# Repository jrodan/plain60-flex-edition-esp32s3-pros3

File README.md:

# Plain60 Flex Edition rev2.2

## Customizing

Changed the PCB to be able to use the proS3 controller https://esp32s3.com/pros3.html and provide I2C ports and the side of the pcb together with 3 PINs directly accessible via PCB for RGB underglow lights. 

| LCSC part # | Description   | Value | Package  | Amount |
| ----------- | ------------- | ----- | -------- | ------:|
| C109001     | Diode         |       | 0805     | 65     |

## General

This universal 60% PCB is designed to support as little layouts as possible without limiting usability for most users. The reason I did this is because other PCBs made for this form factor usually have so many supported layouts that it could almost qualify as swiss cheese.

It also features a fuse and an ESD protection chip to protect the MCU and other parts of the PCB.

## Features
- Fits in the TGR Unikorn
- Compatible with QMK Firmware and VIA Configurator (if you flash a VIA compatible .hex file)
- Compatible with most universal 60% cases and HHKB/WKL Tofu by KBDfans
- USB type-C
- Optional JST header for connection with daughterboard
- Footprint for optional speaker (AST1109MLTRQ)
- ESD protection and fuse
- No LEDs and no underglow
- Minimal layout support
- ISP header

## Supported layouts

## Building
If you feel like building a few of these PCBs yourself, go to the 'Releases' tab and download the latest gerber files. Order those at your favourite PCB manufacturer, get the components needed (see below) and solder them on! A hot air station is not required but a soldering iron is. Flux is recommended.

## Opening the project
To open the files you will need the latest KiCAD nightly version.

## Bill of materials (BOM)
Amount is per PCB, multiply as needed.

| LCSC part # | Description   | Value | Package  | Amount |
| ----------- | ------------- | ----- | -------- | ------:|
| C128353     | Capacitor     | 0.1uF | 0805     | 4      |
| C131056     | Capacitor     | 4.7uF | 0805     | 1      |
| C215803     | Capacitor     | 1uF   | 0805     | 1      |
| C109001     | Diode         |       | 0805     | 65     |
| C261942     | Fuse          |       | 0805     | 1      |
| C165948     | Connector     |       | SMD/THT  | 1      |
| C103904     | Resistor      | 10K   | 0805     | 2      |
| C212411     | Resistor      | 5.1K  | 0805     | 2      |
| C325772     | Resistor      | 22    | 0805     | 2      |
| C44854      | MCU           | 32U4  | QFP-44   | 1      |
| C7519       | ESD chip      |       | SOT23-6  | 1      |
| C341521     | Resonator     | 16MHz | SMD      | 1      |
| C92584      | Switch        |       | SMD      | 1      |
| C160404     | Optional JST  |       | SMD      | 1      |

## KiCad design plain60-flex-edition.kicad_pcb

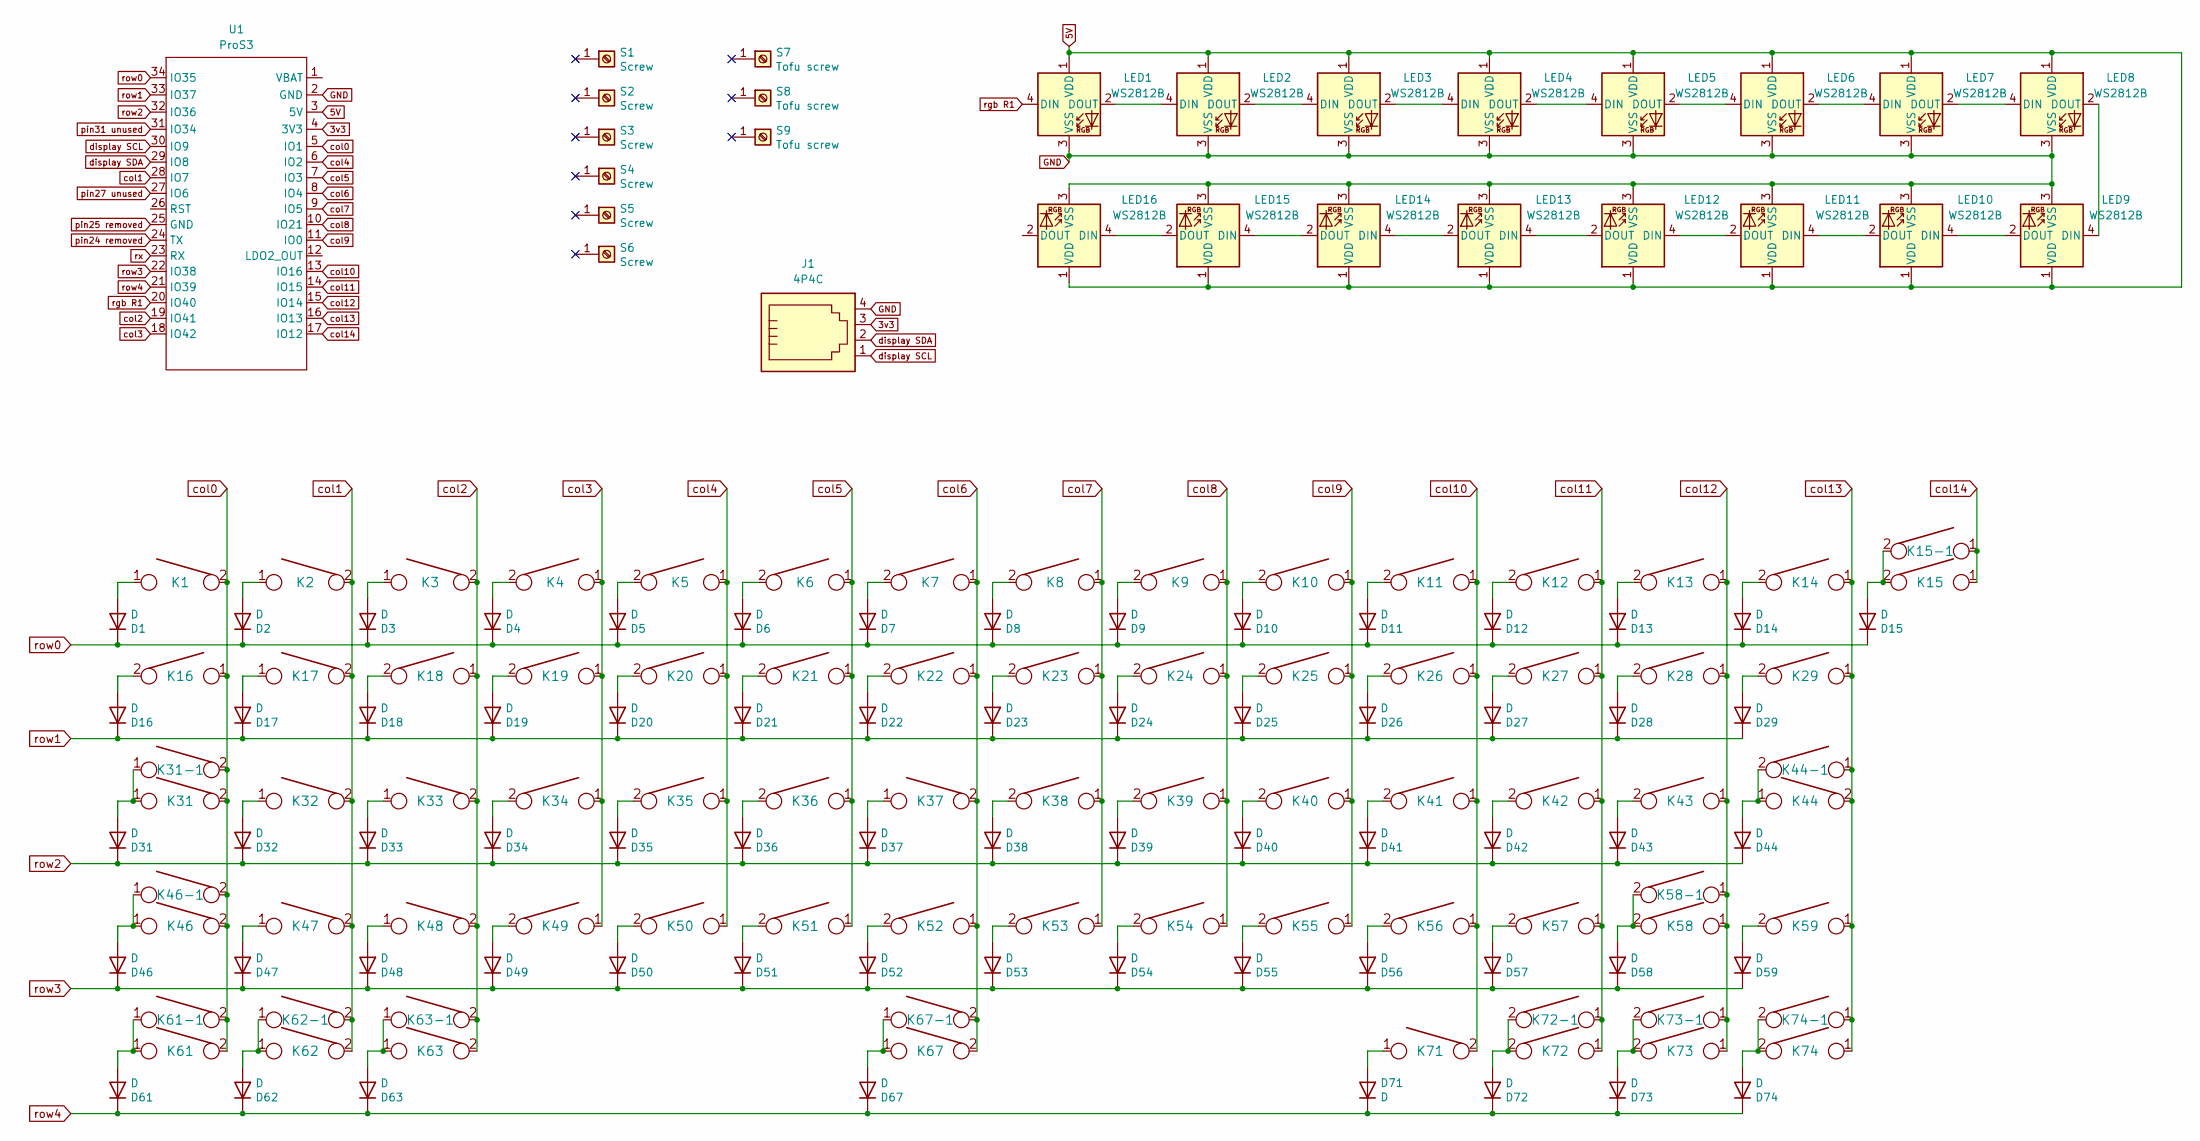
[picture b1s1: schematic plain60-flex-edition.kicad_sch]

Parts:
D1, D2, D3, D4, D5, D6, D7, D8, D9, D10, D11, D12, D13, D14, D15, D16, D17, D18, D19, D20, D21, D22, D23, D24, D25, D26, D27, D28, D29, D31, D32, D33, D34, D35, D36, D37, D38, D39, D40, D41, D42, D43, D44, D46, D47, D48, D49, D50, D51, D52, D53, D54, D55, D56, D57, D58, D59, D61, D62, D63, D67, D71, D72, D73, D74: D; D_0805
J1: 4P4C; JST_PH_S4B-PH-K_1x04_P2.00mm_Horizontal
K1, K2, K3, K4, K5, K6, K7, K8, K9, K10, K11, K12, K13, K14, K15-1, K17, K18, K19, K20, K21, K22, K23, K24, K25, K26, K27, K28, K32, K33, K34, K35, K36, K37, K38, K39, K40, K41, K42, K43, K47, K48, K49, K50, K51, K52, K53, K54, K55, K56, K57, K59, K62-1, K73-1: KEYSW; CHERRY_PLATE_100H
K15: KEYSW; CHERRY_PCB_200H
K16, K29, K61-1, K63-1, K72-1, K74-1: KEYSW; CHERRY_PLATE_150H
K31, K58-1: KEYSW; CHERRY_PLATE_175H
K31-1, K46-1, K61, K62, K63, K71, K72, K73, K74: KEYSW; CHERRY_PLATE_125H
K44: KEYSW; CHERRY_PCB_225H_F
K44-1: KEYSW; CHERRY_PCB_200H_V
K46: KEYSW; CHERRY_PCB_225H
K58: KEYSW; CHERRY_PCB_275H
K67: KEYSW; CHERRY_PCB_625H_F
K67-1: KEYSW; CHERRY_PCB_700H_F
LED1, LED2, LED3, LED4, LED5, LED6, LED7, LED8, LED9, LED10, LED11, LED12, LED13, LED14, LED15, LED16: WS2812B; LED_WS2812B_PLCC4_5.0x5.0mm_P3.2mm
S1, S2, S3, S6: Screw; 5.5_5x2.5mm
S4, S5: Screw; 10x5_7x2.5mm
S7, S8, S9: Tofu screw; 5.5_5x2.5mm
U1: ProS3; ProS3_TH

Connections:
3v3: J1.3, U1.4 (3V3)
5V: LED1.1 (VDD), LED2.1 (VDD), LED3.1 (VDD), LED4.1 (VDD), LED5.1 (VDD), LED6.1 (VDD), LED7.1 (VDD), LED8.1 (VDD), LED9.1 (VDD), LED10.1 (VDD), LED11.1 (VDD), LED12.1 (VDD), LED13.1 (VDD), LED14.1 (VDD), LED15.1 (VDD), LED16.1 (VDD), U1.3 (5V)
GND: J1.4, LED1.3 (VSS), LED2.3 (VSS), LED3.3 (VSS), LED4.3 (VSS), LED5.3 (VSS), LED6.3 (VSS), LED7.3 (VSS), LED8.3 (VSS), LED9.3 (VSS), LED10.3 (VSS), LED11.3 (VSS), LED12.3 (VSS), LED13.3 (VSS), LED14.3 (VSS), LED15.3 (VSS), LED16.3 (VSS), U1.2 (GND)
unnamed: D1.2 (A), K1.1
unnamed: D2.2 (A), K2.1
unnamed: D3.2 (A), K3.1
unnamed: D4.2 (A), K4.2
unnamed: D5.2 (A), K5.2
unnamed: D6.2 (A), K6.2
unnamed: D7.2 (A), K7.2
unnamed: D8.2 (A), K8.2
unnamed: D9.2 (A), K9.2
unnamed: D10.2 (A), K10.2
unnamed: D11.2 (A), K11.2
unnamed: D12.2 (A), K12.2
unnamed: D13.2 (A), K13.2
unnamed: D14.2 (A), K14.2
unnamed: D15.2 (A), K15.2, K15-1.2
unnamed: D16.2 (A), K16.2
unnamed: D17.2 (A), K17.1
unnamed: D18.2 (A), K18.2
unnamed: D19.2 (A), K19.2
unnamed: D20.2 (A), K20.2
unnamed: D21.2 (A), K21.2
unnamed: D22.2 (A), K22.2
unnamed: D23.2 (A), K23.2
unnamed: D24.2 (A), K24.2
unnamed: D25.2 (A), K25.2
unnamed: D26.2 (A), K26.2
unnamed: D27.2 (A), K27.2
unnamed: D28.2 (A), K28.2
unnamed: D29.2 (A), K29.2
unnamed: D31.2 (A), K31.1, K31-1.1
unnamed: D32.2 (A), K32.1
unnamed: D33.2 (A), K33.1
unnamed: D34.2 (A), K34.2
unnamed: D35.2 (A), K35.2
unnamed: D36.2 (A), K36.2
unnamed: D37.2 (A), K37.1
unnamed: D38.2 (A), K38.2
unnamed: D39.2 (A), K39.2
unnamed: D40.2 (A), K40.2
unnamed: D41.2 (A), K41.2
unnamed: D42.2 (A), K42.2
unnamed: D43.2 (A), K43.2
unnamed: D44.2 (A), K44.1, K44-1.2
unnamed: D46.2 (A), K46.1, K46-1.1
unnamed: D47.2 (A), K47.1
unnamed: D48.2 (A), K48.1
unnamed: D49.2 (A), K49.2
unnamed: D50.2 (A), K50.2
unnamed: D51.2 (A), K51.2
unnamed: D52.2 (A), K52.2
unnamed: D53.2 (A), K53.2
unnamed: D54.2 (A), K54.2
unnamed: D55.2 (A), K55.2
unnamed: D56.2 (A), K56.2
unnamed: D57.2 (A), K57.2
unnamed: D58.2 (A), K58.2, K58-1.2
unnamed: D59.2 (A), K59.2
unnamed: D61.2 (A), K61.1, K61-1.1
unnamed: D62.2 (A), K62.1, K62-1.1
unnamed: D63.2 (A), K63.1, K63-1.1
unnamed: D67.2 (A), K67.1, K67-1.1
unnamed: D71.2 (A), K71.1
unnamed: D72.2 (A), K72.2, K72-1.2
unnamed: D73.2 (A), K73.2, K73-1.2
unnamed: D74.2 (A), K74.2, K74-1.2
unnamed: LED1.2 (DOUT), LED2.4 (DIN)
unnamed: LED2.2 (DOUT), LED3.4 (DIN)
unnamed: LED3.2 (DOUT), LED4.4 (DIN)
unnamed: LED4.2 (DOUT), LED5.4 (DIN)
unnamed: LED5.2 (DOUT), LED6.4 (DIN)
unnamed: LED6.2 (DOUT), LED7.4 (DIN)
unnamed: LED7.2 (DOUT), LED8.4 (DIN)
unnamed: LED8.2 (DOUT), LED9.4 (DIN)
unnamed: LED10.2 (DOUT), LED11.4 (DIN)
unnamed: LED9.2 (DOUT), LED10.4 (DIN)
unnamed: LED11.2 (DOUT), LED12.4 (DIN)
unnamed: LED12.2 (DOUT), LED13.4 (DIN)
unnamed: LED13.2 (DOUT), LED14.4 (DIN)
unnamed: LED14.2 (DOUT), LED15.4 (DIN)
unnamed: LED15.2 (DOUT), LED16.4 (DIN)
col0: K1.2, K16.1, K31.2, K31-1.2, K46.2, K46-1.2, K61.2, K61-1.2, U1.5 (IO1)
col1: K2.2, K17.2, K32.2, K47.2, K62.2, K62-1.2, U1.28 (IO7)
col2: K3.2, K18.1, K33.2, K48.2, K63.2, K63-1.2, U1.19 (IO41)
col3: K4.1, K19.1, K34.1, K49.1, U1.18 (IO42)
col4: K5.1, K20.1, K35.1, K50.1, U1.6 (IO2)
col5: K6.1, K21.1, K36.1, K51.1, U1.7 (IO3)
col6: K7.1, K22.1, K37.2, K52.1, K67.2, K67-1.2, U1.8 (IO4)
col7: K8.1, K23.1, K38.1, K53.1, U1.9 (IO5)
col8: K9.1, K24.1, K39.1, K54.1, U1.10 (IO21)
col9: K10.1, K25.1, K40.1, K55.1, U1.11 (IO0)
col10: K11.1, K26.1, K41.1, K56.1, K71.2, U1.13 (IO16)
col11: K12.1, K27.1, K42.1, K57.1, K72.1, K72-1.1, U1.14 (IO15)
col12: K13.1, K28.1, K43.1, K58.1, K58-1.1, K73.1, K73-1.1, U1.15 (IO14)
col13: K14.1, K29.1, K44.2, K44-1.1, K59.1, K74.1, K74-1.1, U1.16 (IO13)
col14: K15.1, K15-1.1, U1.17 (IO12)
display SCL: J1.1, U1.30 (IO9)
display SDA: J1.2, U1.29 (IO8)
pin27 unused: U1.27 (IO6)
pin31 unused: U1.31 (IO34)
rgb R1: LED1.4 (DIN), U1.20 (IO40)
row0: D1.1 (K), D2.1 (K), D3.1 (K), D4.1 (K), D5.1 (K), D6.1 (K), D7.1 (K), D8.1 (K), D9.1 (K), D10.1 (K), D11.1 (K), D12.1 (K), D13.1 (K), D14.1 (K), D15.1 (K), U1.34 (IO35)
row1: D16.1 (K), D17.1 (K), D18.1 (K), D19.1 (K), D20.1 (K), D21.1 (K), D22.1 (K), D23.1 (K), D24.1 (K), D25.1 (K), D26.1 (K), D27.1 (K), D28.1 (K), D29.1 (K), U1.33 (IO37)
row2: D31.1 (K), D32.1 (K), D33.1 (K), D34.1 (K), D35.1 (K), D36.1 (K), D37.1 (K), D38.1 (K), D39.1 (K), D40.1 (K), D41.1 (K), D42.1 (K), D43.1 (K), D44.1 (K), U1.32 (IO36)
row3: D46.1 (K), D47.1 (K), D48.1 (K), D49.1 (K), D50.1 (K), D51.1 (K), D52.1 (K), D53.1 (K), D54.1 (K), D55.1 (K), D56.1 (K), D57.1 (K), D58.1 (K), D59.1 (K), U1.22 (IO38)
row4: D61.1 (K), D62.1 (K), D63.1 (K), D67.1 (K), D71.1 (K), D72.1 (K), D73.1 (K), D74.1 (K), U1.21 (IO39)
rx: U1.23 (RX)

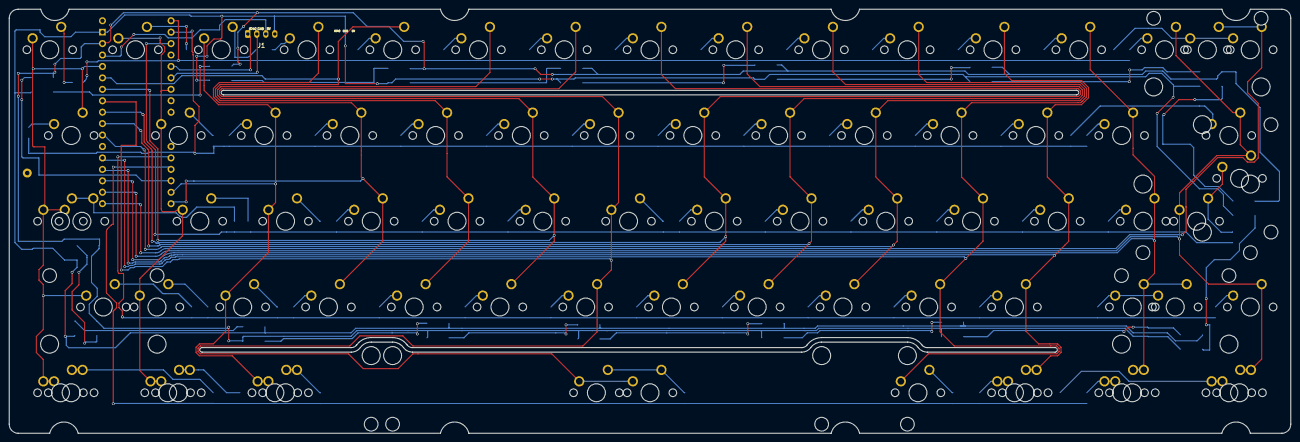
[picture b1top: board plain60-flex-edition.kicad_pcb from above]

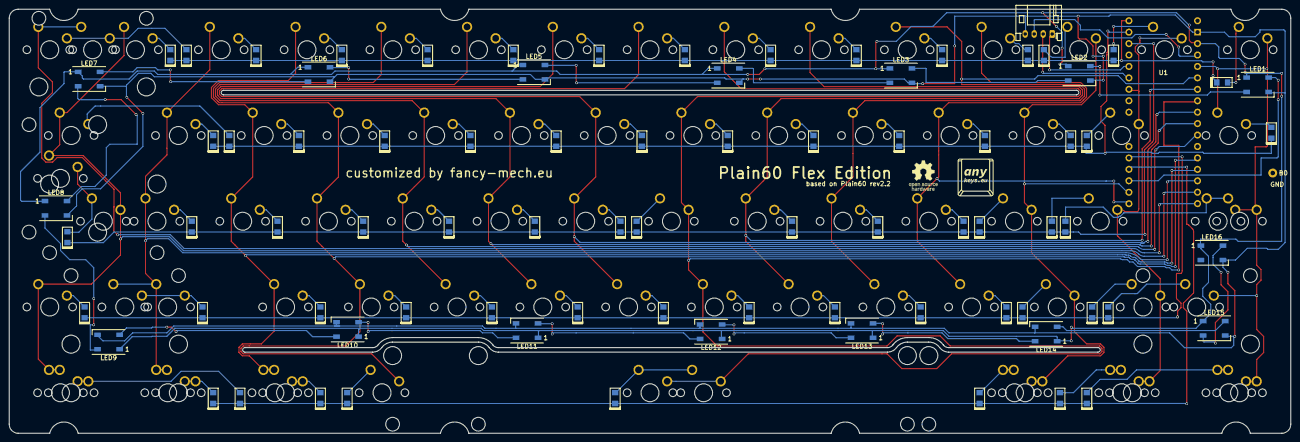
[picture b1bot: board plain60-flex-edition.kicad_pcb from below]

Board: 2 copper layers, 284.7 x 94.2 mm, 169 parts (84 on the bottom side), 106 nets.

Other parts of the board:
H1: B0; free_pin

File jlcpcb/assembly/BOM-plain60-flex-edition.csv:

Comment,Designator,Footprint,LCSC
D,"D1,D10,D11,D12,D13,D14,D15,D16,D17,D18,D19,D2,D20,D21,D22,D23,D24,D25,D26,D27,D28,D29,D3,D31,D32,D33,D34,D35,D36,D37,D38,D39,D4,D40,D41,D42,D43,D44,D46,D47,D48,D49,D5,D50,D51,D52,D53,D54,D55,D56,D57,D58,D59,D6,D61,D62,D63,D67,D7,D71,D72,D73,D74,D8,D9",D_0805,C109001
4P4C,J1,JST_PH_S4B-PH-K_1x04_P2.00mm_Horizontal,C157926
WS2812B,"LED1,LED10,LED11,LED12,LED13,LED14,LED15,LED16,LED2,LED3,LED4,LED5,LED6,LED7,LED8,LED9",LED_WS2812B_PLCC4_5.0x5.0mm_P3.2mm,C2843785
KEYSW,K12,CHERRY_PLATE_100H,
KEYSW,K19,CHERRY_PLATE_100H,
KEYSW,K20,CHERRY_PLATE_100H,
KEYSW,K23,CHERRY_PLATE_100H,
KEYSW,K24,CHERRY_PLATE_100H,
KEYSW,K17,CHERRY_PLATE_100H,
KEYSW,K22,CHERRY_PLATE_100H,
KEYSW,K21,CHERRY_PLATE_100H,
KEYSW,K18,CHERRY_PLATE_100H,
KEYSW,K16,CHERRY_PLATE_150H,
KEYSW,K15,CHERRY_PCB_200H,
KEYSW,K8,CHERRY_PLATE_100H,
KEYSW,K10,CHERRY_PLATE_100H,
KEYSW,K14,CHERRY_PLATE_100H,
KEYSW,K5,CHERRY_PLATE_100H,
KEYSW,K13,CHERRY_PLATE_100H,
KEYSW,K11,CHERRY_PLATE_100H,
KEYSW,K9,CHERRY_PLATE_100H,
KEYSW,K7,CHERRY_PLATE_100H,
KEYSW,K6,CHERRY_PLATE_100H,
KEYSW,K4,CHERRY_PLATE_100H,
KEYSW,K2,CHERRY_PLATE_100H,
KEYSW,K1,CHERRY_PLATE_100H,
KEYSW,K3,CHERRY_PLATE_100H,
KEYSW,K62-1,CHERRY_PLATE_100H,
KEYSW,K71,CHERRY_PLATE_125H,
KEYSW,K53,CHERRY_PLATE_100H,
KEYSW,K58-1,CHERRY_PLATE_175H,
KEYSW,K57,CHERRY_PLATE_100H,
KEYSW,K54,CHERRY_PLATE_100H,
KEYSW,K56,CHERRY_PLATE_100H,
KEYSW,K52,CHERRY_PLATE_100H,
KEYSW,K55,CHERRY_PLATE_100H,
KEYSW,K61-1,CHERRY_PLATE_150H,
KEYSW,K15-1,CHERRY_PLATE_100H,
KEYSW,K74,CHERRY_PLATE_125H,
KEYSW,K73,CHERRY_PLATE_125H,
KEYSW,K28,CHERRY_PLATE_100H,
KEYSW,K48,CHERRY_PLATE_100H,
KEYSW,K25,CHERRY_PLATE_100H,
KEYSW,K36,CHERRY_PLATE_100H,
KEYSW,K33,CHERRY_PLATE_100H,
KEYSW,K63,CHERRY_PLATE_125H,
KEYSW,K44,CHERRY_PCB_225H_F,
KEYSW,K72,CHERRY_PLATE_125H,
KEYSW,K59,CHERRY_PLATE_100H,
KEYSW,K39,CHERRY_PLATE_100H,
KEYSW,K61,CHERRY_PLATE_125H,
KEYSW,K29,CHERRY_PLATE_150H,
KEYSW,K27,CHERRY_PLATE_100H,
KEYSW,K63-1,CHERRY_PLATE_150H,
KEYSW,K50,CHERRY_PLATE_100H,
KEYSW,K34,CHERRY_PLATE_100H,
KEYSW,K47,CHERRY_PLATE_100H,
KEYSW,K43,CHERRY_PLATE_100H,
KEYSW,K38,CHERRY_PLATE_100H,
KEYSW,K35,CHERRY_PLATE_100H,
KEYSW,K32,CHERRY_PLATE_100H,
KEYSW,K40,CHERRY_PLATE_100H,
KEYSW,K46,CHERRY_PCB_225H,
KEYSW,K42,CHERRY_PLATE_100H,
KEYSW,K41,CHERRY_PLATE_100H,
KEYSW,K26,CHERRY_PLATE_100H,
KEYSW,K37,CHERRY_PLATE_100H,
KEYSW,K51,CHERRY_PLATE_100H,
KEYSW,K73-1,CHERRY_PLATE_100H,
KEYSW,K62,CHERRY_PLATE_125H,
KEYSW,K49,CHERRY_PLATE_100H,
KEYSW,K72-1,CHERRY_PLATE_150H,
KEYSW,K74-1,CHERRY_PLATE_150H,
Screw,S5,10x5_7x2.5mm,
KEYSW,K58,CHERRY_PCB_275H,
KEYSW,K67,CHERRY_PCB_625H_F,
Tofu screw,S8,5.5_5x2.5mm,
Tofu screw,S7,5.5_5x2.5mm,
Tofu screw,S9,5.5_5x2.5mm,
Screw,S2,5.5_5x2.5mm,
Screw,S1,5.5_5x2.5mm,
Screw,S3,5.5_5x2.5mm,
Screw,S6,5.5_5x2.5mm,
KEYSW,K67-1,CHERRY_PCB_700H_F,
KEYSW,K44-1,CHERRY_PCB_200H_V,
KEYSW,K31-1,CHERRY_PLATE_125H,
KEYSW,K31,CHERRY_PLATE_175H,
Screw,S4,10x5_7x2.5mm,
ProS3,U1,ProS3_TH,

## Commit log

2022-08-12 added first iteration of refactoring
2022-08-12 tuning
2022-08-16 added underglow leds
2022-08-17 fix pins
2022-09-29 fixed JST header direction
